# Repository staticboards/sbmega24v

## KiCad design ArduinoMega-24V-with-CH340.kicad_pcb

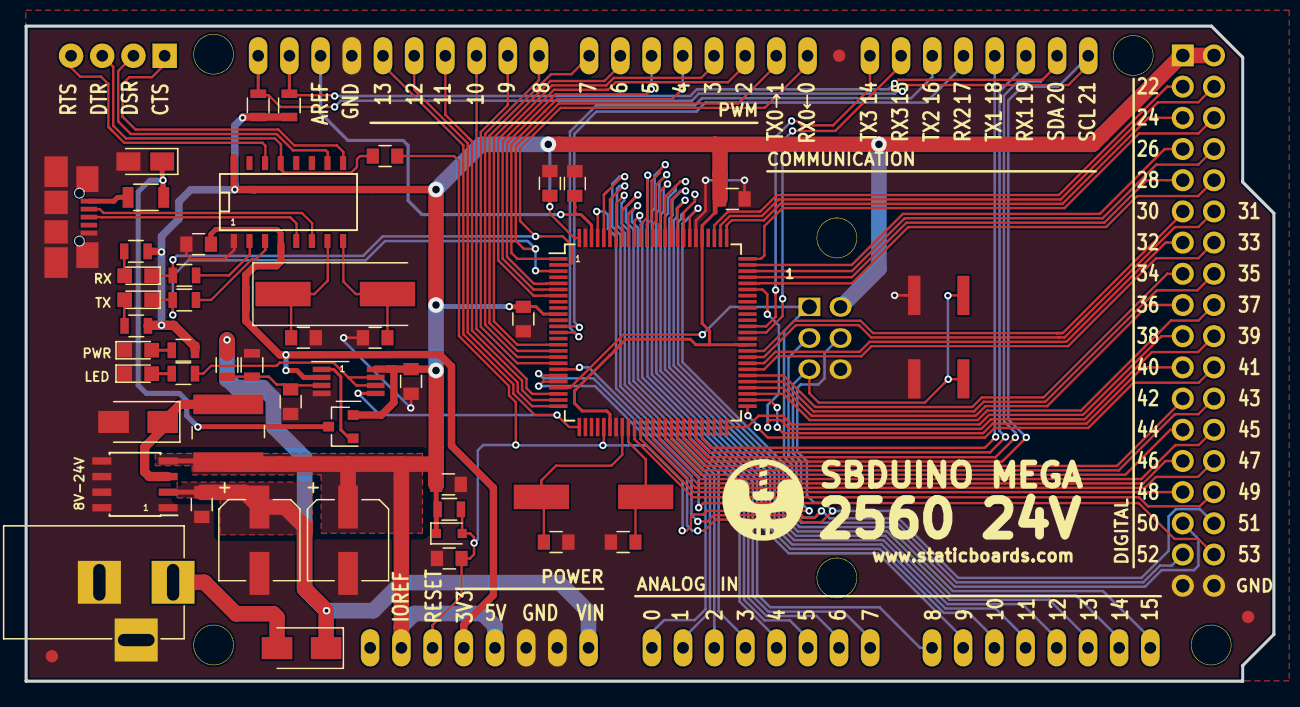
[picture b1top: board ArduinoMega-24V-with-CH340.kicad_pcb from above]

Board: 2 copper layers, 101.6 x 53.3 mm, 63 parts (0 on the bottom side), 99 nets.

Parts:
C1, C9: 100uF/35V; CP_Elec_6.3x7.7
C2, C4, C6, C7, C10, C12, C15, C17: 100nF; C_0805
C3, C18: 100n/50V; C_0805
C5, C8, C11, C13, C16: 22pF; C_0805
C14: 10uF/16V; CP_Tantalum_Case-A_EIA-3216-18_Reflow
D1, D7: B260A; D_SMA
D2: 1N4148; D_SOD-323
D3: PWR; LED_0805
D4: LED; LED_0805
D5: TX; LED_0805
D6: RX; LED_0805
F1: Fuse PPTC 6V 0.5A; R_1206
IC1: ATMEGA2560-16AU; TQFP-100_14x14mm_Pitch0.5mm
J1: BARREL_JACK
J2: CONN_02X18; SDL-136-X-XX_2x18
J3, J5, J7, J8, J9: CONN_1x8; SL-110-X-XX_1x8
J4: CONN_02X03; SDL-106-X-XX_2x03
J6: CONN_01X10; SL-110-X-XX_1x10
J10: CONN_01X04; SL-104-X-XX_1x04
J11, J12, J13, J14, J15, J16: Mount; Hole_3.2mm
L1: 68uH/1.5A; Murata_1255AY-680M=P3
P1: MINI-USB; USB_Micro-B-HOLES
Q1: MOSFET P-CH 20V 2A; SOT-23
R1, R2, R4, R5, R6: 10K; R_0805
R3, R7, R8, R9, R10, R11: 1K; R_0805
SW1: SW_SPST_EVPBF
U1: LMV358; VSSOP-8_3.0x3.0mm_Pitch0.65mm
U2: MIC4680; SOIC-8_3.9x4.9mm_Pitch1.27mm
U4: CH340G; SO-16-N
Y1: 16MHz; Crystal_SMD_HC49-SD
Y2: 12MHz; Crystal_SMD_HC49-SD

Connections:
+3V3: C15.1, J3.4, U1.2, U4.4
+5V: C2.1, C6.1, C7.1, C9.1, C12.2, C18.1, D2.1, IC1.10, IC1.31, IC1.61, IC1.80, IC1.100, J2.1, J2.2, J3.2, J3.5, J4.2, L1.2, Q1.2, R4.2, R5.2, R6.2, R7.2, R10.1, R11.1, U1.8, U2.4, U4.16
/ADC0: IC1.97, J9.1
/ADC1: IC1.96, J9.2
/ADC2: IC1.95, J9.3
/ADC3: IC1.94, J9.4
/ADC4: IC1.93, J9.5
/ADC5: IC1.92, J9.6
/ADC6: IC1.91, J9.7
/ADC7: IC1.90, J9.8
/ADC8: IC1.89, J5.1
/ADC9: IC1.88, J5.2
/ADC10: IC1.87, J5.3
/ADC11: IC1.86, J5.4
/ADC12: IC1.85, J5.5
/ADC13: IC1.84, J5.6
/ADC14: IC1.83, J5.7
/ADC15: IC1.82, J5.8
/AREF: C4.1, IC1.98, J6.3
/CMP: C10.1, R1.1, R2.2, U1.3
/CTS: J10.1, U4.9
/D+: P1.3, U4.5
/D-: P1.2, U4.6
/DSR: J10.2, U4.10
/DTR: C17.2, J10.3, U4.13
/PA0: IC1.78, J2.3
/PA1: IC1.77, J2.4
/PA2: IC1.76, J2.5
/PA3: IC1.75, J2.6
/PA4: IC1.74, J2.7
/PA5: IC1.73, J2.8
/PA6: IC1.72, J2.9
/PA7: IC1.71, J2.10
/PB0: IC1.19, J2.34
/PB1: IC1.20, J2.33, J4.3
/PB2: IC1.21, J2.32, J4.4
/PB3: IC1.22, J2.31, J4.1
/PB4: IC1.23, J6.8
/PB5: IC1.24, J6.7
/PB6: IC1.25, J6.6
/PB7: IC1.26, J6.5, U1.5
/PC0: IC1.53, J2.18
/PC1: IC1.54, J2.17
/PC2: IC1.55, J2.16
/PC3: IC1.56, J2.15
/PC4: IC1.57, J2.14
/PC5: IC1.58, J2.13
/PC6: IC1.59, J2.12
/PC7: IC1.60, J2.11
/PD7: IC1.50, J2.19
/PE0: D6.1, IC1.2, J8.1, R3.1
/PE1: D5.1, IC1.3, J8.2, R9.1
/PE3: IC1.5, J8.6
/PE4: IC1.6, J8.3
/PE5: IC1.7, J8.4
/PG0: IC1.51, J2.22
/PG1: IC1.52, J2.21
/PG2: IC1.70, J2.20
/PG5: IC1.1, J8.5
/PH3: IC1.15, J8.7
/PH4: IC1.16, J8.8
/PH5: IC1.17, J6.10
/PH6: IC1.18, J6.9
/PL0: IC1.35, J2.30
/PL1: IC1.36, J2.29
/PL2: IC1.37, J2.28
/PL3: IC1.38, J2.27
/PL4: IC1.39, J2.26
/PL5: IC1.40, J2.25
/PL6: IC1.41, J2.24
/PL7: IC1.42, J2.23
/RESET: C5.1, C17.1, D2.2, IC1.30, J3.3, J4.5, R4.1, SW1.3, SW1.4
/RTS: J10.4, U4.14
/RXD1: IC1.45, J7.3
/RXD2: IC1.12, J7.5
/RXD3: IC1.63, J7.7
/SCL: IC1.43, J6.1, J7.1, R5.1
/SDA: IC1.44, J6.2, J7.2, R6.1
/TXD1: IC1.46, J7.4
/TXD2: IC1.13, J7.6
/TXD3: IC1.64, J7.8
/USBVCC: C14.1, F1.2, Q1.3
GND: C1.2, C2.2, C3.2, C4.2, C5.2, C6.2, C7.2, C8.2, C9.2, C10.2, C11.2, C12.1, C13.2, C14.2, C15.2, C16.2, C18.2, D1.2, D3.1, D4.1, IC1.11, IC1.32, IC1.62, IC1.81, IC1.99, J1.2, J1.3, J2.35, J2.36, J3.6, J3.7, J4.6, J6.4, P1.5, P1.6, R2.1, SW1.1, SW1.2, U1.4, U2.1, U2.5, U2.6, U2.7, U2.8, U4.1
unnamed: C8.1, IC1.33, Y1.1
unnamed: C11.1, U4.7, Y2.1
unnamed: C13.1, IC1.34, Y1.2
unnamed: C16.1, U4.8, Y2.2
unnamed: D1.1, L1.1, U2.3
unnamed: D3.2, R7.1
unnamed: D4.2, R8.1
unnamed: D5.2, R10.2
unnamed: D6.2, R11.2
unnamed: D7.2, J1.1
unnamed: F1.1, P1.1
unnamed: Q1.1, U1.1
unnamed: R3.2, U4.2
unnamed: R8.2, U1.6, U1.7
unnamed: R9.2, U4.3
VIN: C1.1, C3.1, D7.1, J3.8, R1.2, U2.2

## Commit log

2019-02-28 initial
2019-02-28 kicad5 windows version
